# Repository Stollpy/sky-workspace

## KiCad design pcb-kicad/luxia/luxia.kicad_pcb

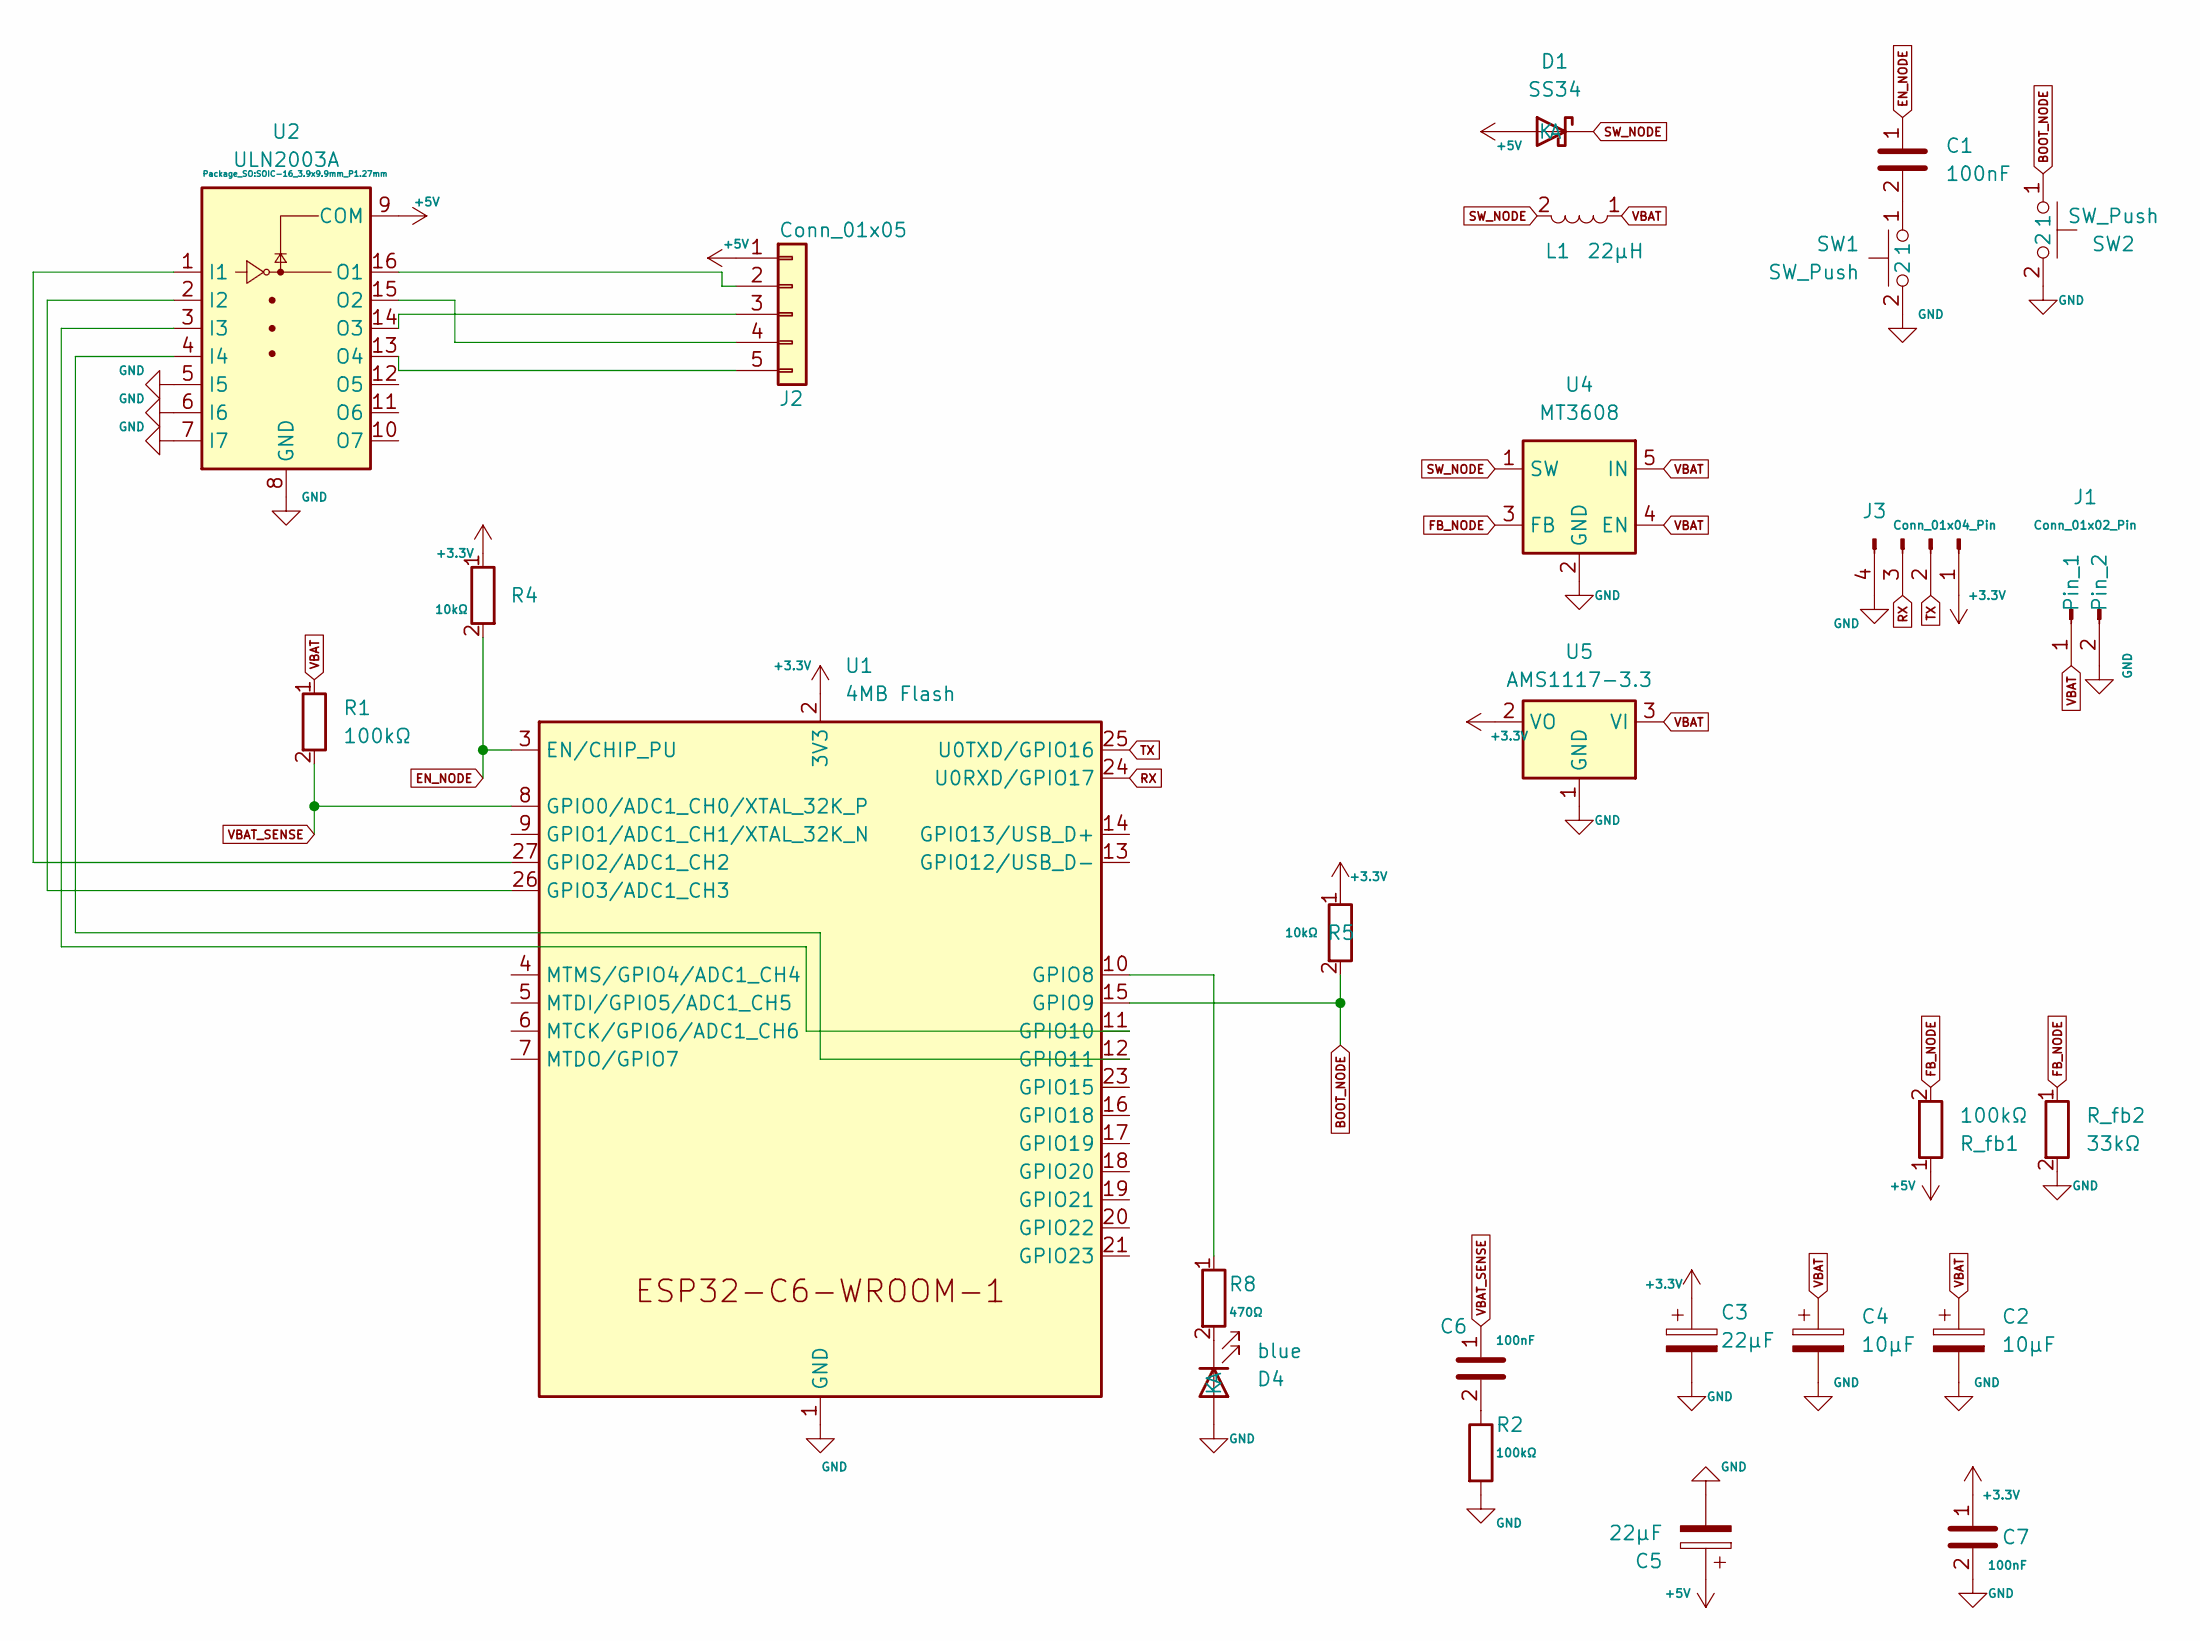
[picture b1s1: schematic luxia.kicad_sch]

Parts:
C1, C6, C7: 100nF; C_0603_1608Metric_Pad1.08x0.95mm_HandSolder
C2, C4: 10µF; C_0805_2012Metric_Pad1.18x1.45mm_HandSolder
C3, C5: 22µF; C_0805_2012Metric_Pad1.18x1.45mm_HandSolder
D1: SS34; D_SMA
D4: blue; LED_0603_1608Metric_Pad1.05x0.95mm_HandSolder
J1: Conn_01x02_Pin; PinHeader_1x02_P2.54mm_Vertical
J2: Conn_01x05; JST_XH_B5B-XH-A_1x05_P2.50mm_Vertical
J3: Conn_01x04_Pin; PinHeader_1x04_P2.54mm_Vertical
L1: 22µH; L_1210_3225Metric_Pad1.42x2.65mm_HandSolder
R1, R2: 100kΩ; R_0603_1608Metric_Pad0.98x0.95mm_HandSolder
R4, R5: 10kΩ; R_0603_1608Metric_Pad0.98x0.95mm_HandSolder
R8: 470Ω; R_0603_1608Metric_Pad0.98x0.95mm_HandSolder
R_fb1: 100kΩ; R_0603_1608Metric_Pad0.98x0.95mm_HandSolder
R_fb2: 33kΩ; R_0603_1608Metric_Pad0.98x0.95mm_HandSolder
SW1, SW2: SW_Push; SW_Push_1TS009xxxx-xxxx-xxxx_6x6x5mm
U1: 4MB Flash; ESP32-C6-WROOM-1
U2: ULN2003A; SOIC-16_3.9x9.9mm_P1.27mm
U4: MT3608; SOT-23-6
U5: AMS1117-3.3; SOT-223-3_TabPin2

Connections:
+3.3V: C3.1, C7.1, J3.1, R4.1, R5.1, U1.2 (3V3), U5.2 (VO)
+5V: C5.1, D1.2 (A), J2.1, R_fb1.1, U2.9 (COM)
BOOT_NODE: R5.2, SW2.1, U1.15 (GPIO9)
EN_NODE: C1.1, R4.2, U1.3 (EN/CHIP_PU)
FB_NODE: R_fb1.2, R_fb2.1, U4.3 (FB)
GND: C2.2, C3.2, C4.2, C5.2, C7.2, D4.2 (A), J1.2, J3.4, R2.2, R_fb2.2, SW1.2, SW2.2, U1.1 (GND), U1.28 (GND), U1.29 (GND), U2.5 (I5), U2.6 (I6), U2.7 (I7), U2.8 (GND), U4.2 (GND), U5.1 (GND)
unnamed: C1.2, SW1.1
unnamed: C6.2, R2.1
unnamed: D4.1 (K), R8.2
unnamed: J2.2, U2.16 (O1)
unnamed: J2.3, U2.14 (O3)
unnamed: J2.4, U2.15 (O2)
unnamed: J2.5, U2.13 (O4)
unnamed: U1.27 (GPIO2/ADC1_CH2), U2.1 (I1)
unnamed: U1.26 (GPIO3/ADC1_CH3), U2.2 (I2)
unnamed: R8.1, U1.10 (GPIO8)
unnamed: U1.11 (GPIO10), U2.3 (I3)
unnamed: U1.12 (GPIO11), U2.4 (I4)
RX: J3.3, U1.24 (U0RXD/GPIO17)
SW_NODE: D1.1 (K), L1.2, U4.1 (SW)
TX: J3.2, U1.25 (U0TXD/GPIO16)
VBAT: C2.1, C4.1, J1.1, L1.1, R1.1, U4.4 (EN), U4.5 (IN), U5.3 (VI)
VBAT_SENSE: C6.1, R1.2, U1.8 (GPIO0/ADC1_CH0/XTAL_32K_P)

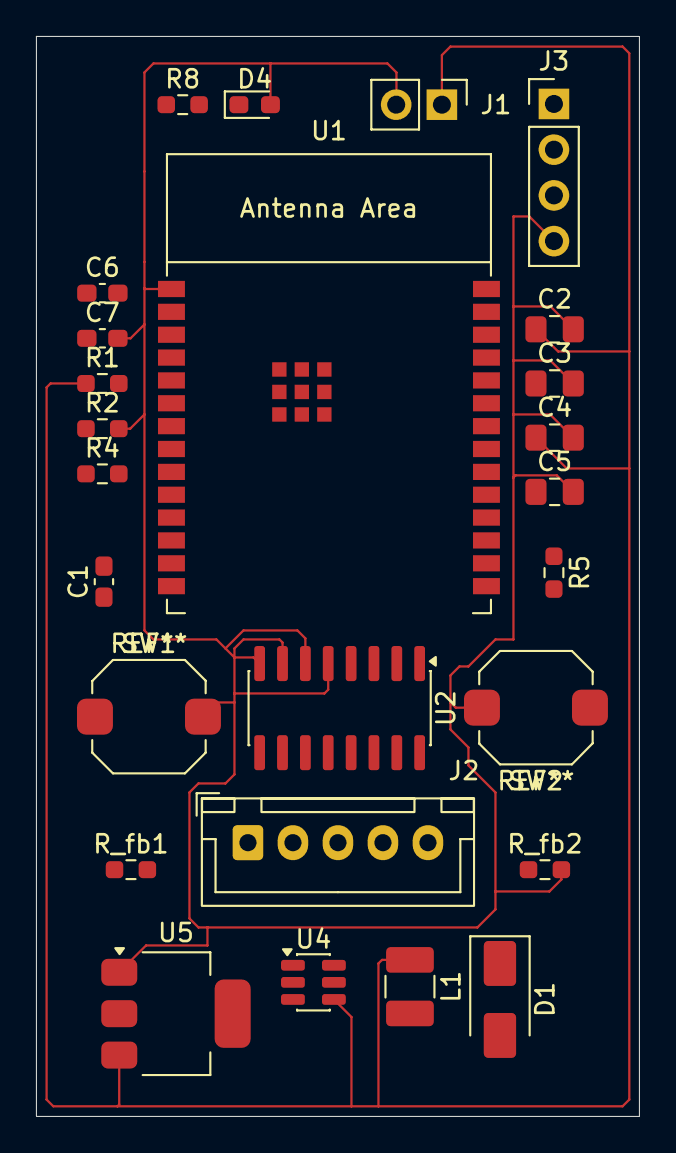
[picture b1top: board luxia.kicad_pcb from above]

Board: 4 copper layers, 33.5 x 60.0 mm, 26 parts (0 on the bottom side), 23 nets.

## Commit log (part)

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2026-03-31 init commit
2026-03-31 refactor: mv .cursor in pcb/.cursor
2026-03-31 feature: added rules and skills for the firmware
2026-03-31 feature: added http server component
2026-03-31 refactor: delete sdkconfig
2026-04-13 feature: added gitignore and cursorignore updates
    Made-with: Cursor
2026-04-13 refactor: extracted luxia http/cmd into dedicated luxia-firmware repo
    Made-with: Cursor
2026-04-13 feature: added jalon-2 firmware repos (sky-proto, sky-framework, sky-c6-firmware, luxia-firmware)
    Made-with: Cursor
2026-04-13 feature: added device-service Rust bridge (serial + Reverb WebSocket)
    Made-with: Cursor
2026-04-13 feature: added device management, pairing workflow and real-time control in Orbit
    Made-with: Cursor
2026-04-13 feature: added device-service Helm chart and infra config
    Made-with: Cursor
2026-04-13 feature: added jalon-2 documentation, dev guides and task specs
    Made-with: Cursor
2026-04-13 feature: added sky repo init scripts and sky-watch-firmware
    Made-with: Cursor
2026-04-13 feature: updated submodule refs (serial ttyAMA0, Reverb config, seeder, dev guides)
    Made-with: Cursor
